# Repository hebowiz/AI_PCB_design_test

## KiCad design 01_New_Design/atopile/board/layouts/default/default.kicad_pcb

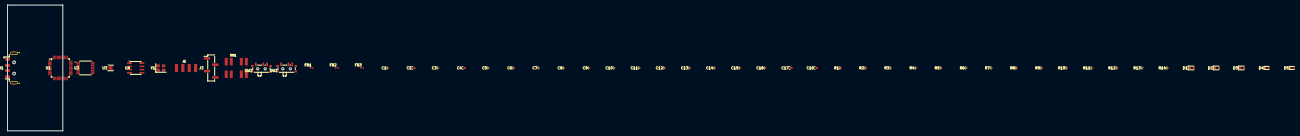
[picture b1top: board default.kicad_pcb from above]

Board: 2 copper layers, 22.0 x 50.0 mm, 51 parts (0 on the bottom side), 38 nets, no tracks yet.

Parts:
C1, C3, C5, C6, C7, C8, C9, C10, C11, C12, C13, C14, C15, C16: C_0402_1005Metric
C2, C4, C17, C18: C_0603_1608Metric
D1, D2, D3: LED_0603_1608Metric
D4, D5: D_SOD-523
FB1, FB2, FB3: L_0402_1005Metric
J1: USB_A_Molex_48037-2200_Horizontal
J2: TSM_104_SH
J3: PinHeader_1x04_P2.54mm_Vertical_SMD_Pin1Left
R1, R2, R3, R4, R5, R6, R7, R8, R9, R10, R11, R12, R13, R14: R_0402_1005Metric
SW1: JS203011SCQN
SW2, SW3: SW_SPDT_PCM12
U1: LQFP-48_7x7mm_P0.5mm
U2: TSSOP-16_4.4x5mm_P0.65mm
U3: WSON-6-1EP_2x2mm_P0.65mm_EP1x1.6mm
U4: SOIC-8_3.9x4.9mm_P1.27mm
Y1: Crystal_SMD_3225-4Pin_3.2x2.5mm

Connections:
CTS_N: J3.3, R7.2, U2.10
EECLK: U1.44, U4.2
EECS: U1.45, U4.1
EEDATA: R3.1, U1.43, U4.3
EEDO: R3.2, R4.2, U4.4
FB: R8.2, R9.1, R10.1, R11.1, U3.2
FT_CTS_N: U1.16, U2.7
FT_RTS_N: U1.15, U2.5
FT_RXD: U1.14, U2.6
FT_TXD: U1.13, U2.4
GND: C1.2, C2.2, C3.2, C4.2, C5.2, C6.2, C7.2, C8.2, C9.2, C10.2, C11.2, C12.2, C13.2, C14.2, C15.2, C16.2, C17.2, C18.2, D1.1, D4.2, D5.2, J1.4, J1.SH, J2.1, J3.1, R1.2, R9.2, SW1.3, U1.4, U1.9, U1.10, U1.11, U1.22, U1.23, U1.35, U1.36, U1.41, U1.42, U1.47, U1.48, U2.3, U2.8, U2.9, U3.3, U3.5, U3.7, U4.5, Y1.2, Y1.4
PWREN_N: R5.2, U1.30, U2.14, U2.15
PWR_LED_A: D1.2, R12.2
REF: R1.1, U1.5
RESET_N: R2.1, U1.34
RTS_N: J3.2, U2.12
RXD: J2.3, R6.2, U2.11
RXLED_N: D3.1, U1.27
RX_LED_A: D3.2, R14.2
SEL_2V5: R10.2, SW1.2
SEL_3V3: R11.2, SW1.4
TXD: J2.2, U2.13
TXLED_N: D2.1, U1.28
TX_LED_A: D2.2, R13.2
USB5V_OUT: J2.4, SW2.2
USB_DM: D4.1, J1.2, U1.6
USB_DP: D5.1, J1.3, U1.7
V3V3: C4.1, C7.1, C8.1, C9.1, C14.1, C16.1, FB2.1, FB3.1, R2.2, R4.1, R5.1, R13.1, R14.1, U1.12, U1.18, U1.19, U1.20, U1.24, U1.31, U1.39, U1.46, U2.1, U2.2, U4.8
VBUS: C1.1, C17.1, FB1.1, J1.1, R12.1, SW2.1, U3.4, U3.6
VBUS_FT: C2.1, C3.1, FB1.2, U1.40
VCCA_1V8: C5.1, U1.37
VCORE_1V8: C6.1, U1.38
VIO: C15.1, C18.1, R6.1, R7.1, R8.1, SW3.1, U2.16, U3.1
VIO_OUT: J3.4, SW3.2
VPHY: C10.1, FB2.2, U1.3
VPLL: C11.1, FB3.2, U1.8
XI: C12.1, U1.1, Y1.1
XO: C13.1, U1.2, Y1.3

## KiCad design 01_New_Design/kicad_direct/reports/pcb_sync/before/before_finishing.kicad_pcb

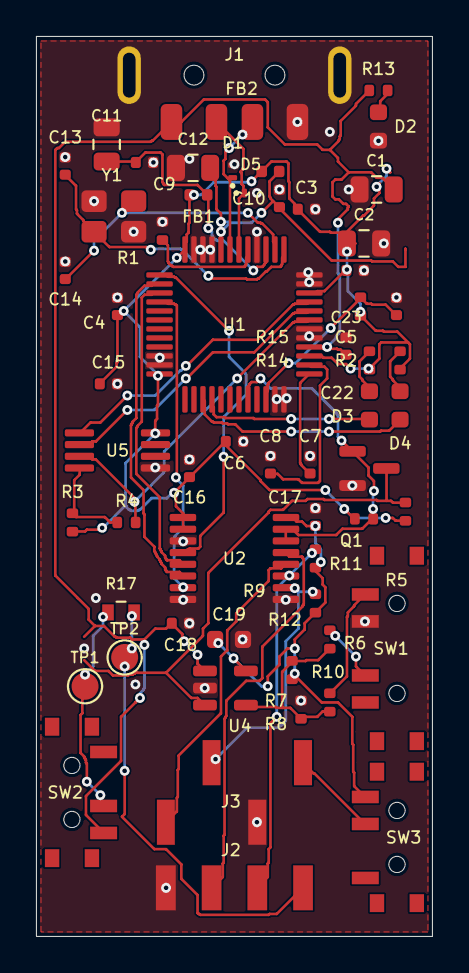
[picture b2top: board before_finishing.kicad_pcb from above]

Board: 2 copper layers, 22.0 x 50.0 mm, 58 parts (0 on the bottom side), 39 nets.

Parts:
C1, C2, C11, C12: 4.7u; C_0805_2012Metric
C3, C4, C5, C6, C7, C8, C9, C10, C15, C16, C17, C22, C23: 100n; C_0402_1005Metric
C13, C14: 15p 1%; C_0402_1005Metric
C18: 1u; C_0402_1005Metric
C19: 2.2u; C_0603_1608Metric
D1, D5: ESD321DPYR; Texas_DPY0002A_0.6x1mm_P0.65mm
D2: RED; LED_0603_1608Metric
D3: GREEN TX; LED_0603_1608Metric
D4: GREEN RX; LED_0603_1608Metric
FB1, FB2: 600R@100MHz; L_0402_1005Metric
J1: USB-A PLUG; USB_A_Molex_48037-2200_Horizontal
J2: GND TXD RXD 5V; TSM_104_SH_PROVISIONAL
J3: RTS CTS GND VIO; PinHeader_1x04_P2.54mm_Vertical_SMD_Pin1Left
Q1: 2N7002; SOT-23
R1: 12k; R_0402_1005Metric
R2, R3, R5, R6, R8, R13: 10k; R_0402_1005Metric
R4: 2.2k; R_0402_1005Metric
R7: 22.6k; R_0402_1005Metric
R9: 17.8k; R_0402_1005Metric
R10: 8.25k; R_0402_1005Metric
R11, R12: 100k; R_0402_1005Metric
R14, R15: 4.7k; R_0402_1005Metric
R17: 0R / 0603; R_0603_Bourns_CRPF
SW1: 1V8 / 2V5 / 3V3; SW_SP3T_PCM13
SW2: USB5V OUT; SW_SPDT_PCM12
SW3: VIO OUT; SW_SPDT_PCM12
TP1, TP2: D1.5mm; TestPoint_Pad_D1.5mm
U1: FT232HL; LQFP-48_7x7mm_P0.5mm
U2: SN74AXC4T245PWR; TSSOP-16_4.4x5mm_P0.65mm
U4: TLV75801PDBV; SOT-23-5
U5: 93LC56B; MSOP-8_3x3mm_P0.65mm
Y1: 12MHz 12pF; Crystal_SMD_3225-4Pin_3.2x2.5mm

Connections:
+3V3: C2.1, C3.1, C4.1, C5.1, C6.1, C15.1, C16.1, FB1.1, FB2.1, R2.1, R3.1, R5.1, R6.1, R14.1, R15.1, U1.12, U1.24, U1.39, U1.46, U2.1, U2.2, U5.8
/CTS_N: J3.2, R12.2, U2.10
/EE_CLK: U1.44, U5.2
/EE_CS: U1.45, U5.1
/EE_DATA: R4.2, U1.43, U5.3
/EE_DO: R3.2, R4.1, U5.4
/FB: R7.2, R8.1, R9.1, R10.1, U4.4
/FB_2V5: R9.2, SW1.2
/FB_3V3: R10.2, SW1.4
/FT_CTS_N: U1.16, U2.7
/FT_RTS_N: U1.15, U2.5
/FT_RXD: U1.14, U2.6
/FT_TXD: U1.13, U2.4
/LED_PWR_A: D2.2, R13.2
/LED_RX_A: D4.2, R15.2
/LED_TX_A: D3.2, R14.2
/PWREN_N: Q1.1, R5.2, U1.32, U2.14, U2.15
/PWR_EN: Q1.3, R6.2, U4.3
/REF12K: R1.1, U1.5
/RESET_N: C22.1, R2.2, U1.34
/RTS_N: J3.1, U2.12
/RXD: J2.3, R11.2, U2.11
/RXLED_N: D4.1, U1.27
/TXD: J2.2, U2.13
/TXLED_N: D3.1, U1.28
/USB5V_SW: R17.1, SW2.2, TP1.1
/USB_D+: D1.1, J1.3, U1.7
/USB_D-: D5.1, J1.2, U1.6
/XTAL_IN: C13.1, U1.1, Y1.1
/XTAL_OUT: C14.1, U1.2, Y1.3
GND: C1.2, C2.2, C3.2, C4.2, C5.2, C6.2, C7.2, C8.2, C9.2, C10.2, C11.2, C12.2, C13.2, C14.2, C15.2, C16.2, C17.2, C18.2, C19.2, C22.2, C23.2, D1.2, D2.1, D5.2, J1.4, J1.SH, J2.1, J3.3, Q1.2, R1.2, R8.2, SW1.3, U1.4, U1.9, U1.10, U1.11, U1.22, U1.23, U1.35, U1.36, U1.41, U1.42, U1.47, U1.48, U2.3, U2.8, U2.9, U4.2, U5.5, Y1.2, Y1.4
USB5V: C1.1, C18.1, C23.1, J1.1, R13.1, SW2.3, U1.40, U4.1
USB5V_OUT: J2.4, R17.2, TP2.1
VCCA_1V8: C7.1, U1.37
VCORE_1V8: C8.1, U1.38
VIO: C17.1, C19.1, R7.1, R11.1, R12.1, SW3.3, U2.16, U4.5
VIO_OUT: J3.4, SW3.2
VPHY: C9.1, C11.1, FB1.2, U1.3
VPLL: C10.1, C12.1, FB2.2, U1.8
